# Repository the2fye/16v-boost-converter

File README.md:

# 16 V Boost Converter for a 2S2P Li-ion Pack

A compact DC-DC boost converter that takes a 2S2P lithium-ion battery pack (7.2 V to 8.4 V) up to a regulated 16 V rail. I designed it as the technical assessment for the hardware team at the UGA Small Satellite Research Laboratory (SSRL), so the design choices lean toward what matters on a CubeSat: small board area, margin on every part, and protecting the battery.

## Specs

| Parameter | Value |
|---|---|
| Input | 7.2 V to 8.4 V (2S2P Li-ion), turn-on near 6.6 V |
| Output | 16 V (15.98 V set point) |
| Output current | 1 A assumed (16 W) |
| Controller | TI TPS55340PWP, HTSSOP-14 with PowerPAD |
| Switching frequency | 500 kHz |
| Duty cycle | 0.49 to 0.56 |
| Peak inductor current | 2.8 A |
| Estimated efficiency | 90% to 92% |
| Calculated output ripple | about 25 mV |
| PCB | 2 layers, 22.7 mm x 20.8 mm |
| Parts cost | about $8.16 per board (qty 1) |

## Design decisions

**Topology.** The input is always below 16 V, so a plain boost is the simplest option that works. I went non-synchronous (Schottky diode instead of a second MOSFET) because at 16 W a synchronous design would add a controller, two FETs, and more board area for a few percent of efficiency.

**Controller.** The TPS55340 has an integrated 5 A / 40 V switch, a 2.9 V to 32 V input range, adjustable frequency, and good TI design support (datasheet equations plus WEBENCH to cross-check). I compared it against the LM2577-ADJ (fixed 52 kHz, needs a much bigger inductor) and a synchronous controller like the LM5122 (more parts and layout complexity).

**Load current.** The assignment didn't give a load current, so I assumed 1 A and designed everything around it. At minimum input the switch and inductor carry about 2.5x the output current, which puts the peak near 2.8 A against the IC's 5.25 A current-limit floor.

**Inductor.** 12 uH Wurth 744393465120, sized for about 30% ripple. I picked it over a Coilcraft XAL8080 and a Bourns SRP1050WA because it had the smallest footprint, a 9.8 A saturation current, and AEC-Q200 qualification.

**Output caps.** Three 22 uF / 25 V X7R 1210 ceramics. Ceramics lose a lot of capacitance under DC bias (each one is closer to 15 uF at 16 V), so three in parallel gives about 45 uF effective and splits the ripple current.

**Feedback.** R1 = 120k, R2 = 10k gives Vout = 1.229 x (1 + 120k/10k) = 15.98 V.

**Battery undervoltage lockout.** The TPS55340's built-in UVLO sits below 3 V, which is way too low for a 2S pack. A boost pulls more current as its input drops, so a dying pack gets pulled down harder. I added a divider on EN (R5 = 51.1k, R6 = 10k) so the converter only runs above about 6.6 V.

**Compensation.** R3, C8, and C10 are starting values from the TI datasheet example. The right-half-plane zero at minimum input puts the crossover limit around 14 kHz, and the final values would come from a measured loop response.

## WEBENCH cross-check

To check my hand calculations, I ran the same specs (7.2 V to 8.4 V in, 16 V at 1 A out) through TI WEBENCH and compared against two TPS55340 designs it generated. WEBENCH picks its own frequency and parts (and used the QFN package), so this is a check on the math, not a copy of my board.

| | My design | WEBENCH design A | WEBENCH design B |
|---|---|---|---|
| Feedback divider | 120k / 10k | 120k / 10k | 120k / 10k |
| Duty cycle | 0.49 to 0.56 | about 0.49 to 0.56 | about 0.49 to 0.56 |
| Switching frequency | 500 kHz | 549 kHz | 779 kHz |
| Frequency resistor | 95.3k | 86.6k | 60.4k |
| Inductor | 12 uH | 10 uH | 6.8 uH |
| Output caps | 3x 22 uF | 2x 22 uF + 1 uF | 3x 4.7 uF |
| Compensation (R / C / C) | 2.55k / 0.1 uF / 100 pF | 976 / 150 nF / 2.7 nF | n/a |
| Efficiency | 90% to 92% (my estimate) | 95% to 96% | 95% to 96% |

What I took from it:

- **The feedback divider and duty cycle match exactly**, so the output setpoint and operating point math checks out.
- **The frequency equation holds.** Plugging 549 kHz into the datasheet equation gives 86.7k, which rounds to WEBENCH's 86.6k. That's the same equation I used to get 95.3k at 500 kHz.
- **The inductor difference comes from frequency, not a mistake.** The same sizing equation gives about 9.6 uH at 549 kHz (so 10 uH works) and about 10.5 uH at 500 kHz (so I rounded up to 12 uH).
- **Frequency barely moved efficiency.** Going from 549 kHz to 779 kHz cut the footprint about 39% with basically the same efficiency curve, which backs up that switching loss is secondary at this power level.
- **I think WEBENCH's efficiency is optimistic.** The Schottky diode alone drops about 0.5 V at 1 A, which is 0.5 W or about 3% of the 16 W output before counting the switch, inductor, or switching losses. I kept my 90% to 92% estimate.
- **For compensation**, I kept the datasheet's worked example values, since those come with documented equations. Either set is a starting point to tune on the bench.

## Schematic

## PCB layout

- Two layers: all parts and almost all routing on top, solid ground pour on the bottom.
- The critical switching loop (SW pins, D1, output caps, back to PGND) is kept under about 1 cm².
- Six thermal vias under the PowerPAD carry heat into the ground plane. This matters more in orbit, where there's no air to carry heat away.
- AGND and PGND join at the PowerPAD. The quiet analog parts return to ground near the IC, away from the switching return.
- No traces or vias under the inductor.
- Test points on the switch node, ground, and FB for bench bring-up.

## Repo contents

```
hardware/      KiCad 9 project (schematic, PCB, project file)
docs/          full design report (PDF) and images
production/    gerbers and BOM
```

The KiCad files open directly. The TPS55340 and Wurth inductor footprints are embedded in the board file.

## Full report

The [design report](docs/Boost_Converter_Design_Report_Aryafar.pdf) covers the full calculations, the inductor trade study, the loss breakdown, and an 11-step bench test procedure. Note that the report lists the board as 22.3 mm wide. The actual outline in the PCB file is 22.7 mm.

## Status and next steps

The design was completed on paper and in KiCad. It hasn't been fabricated yet. Things I'd change for a next revision:

- Finalize the compensation values with a measured loop response
- Add a 0 Ω footprint in series with R1 for loop injection
- Add a load switch so the pack can be fully disconnected at low charge
- Add an input fuse or eFuse for output short protection
- Widen the VIN and switch-node traces, and raise the silkscreen text to the fab minimum
- For flight: TPS55340-Q1, conformal coating, and thermal testing in vacuum

## Tools

KiCad 9, TI WEBENCH, DigiKey and Mouser for part selection.

## Project history

I did this design over about a week in September 2026 for the SSRL assessment and worked on it locally in KiCad without version control. The files here are the final version I submitted, added to GitHub in November 2026 and split into commits by part of the design (schematic, layout, production files, documentation). The only change from the submitted version is a BOM correction listing C1/C2 as X5R, which matches the actual Murata part.

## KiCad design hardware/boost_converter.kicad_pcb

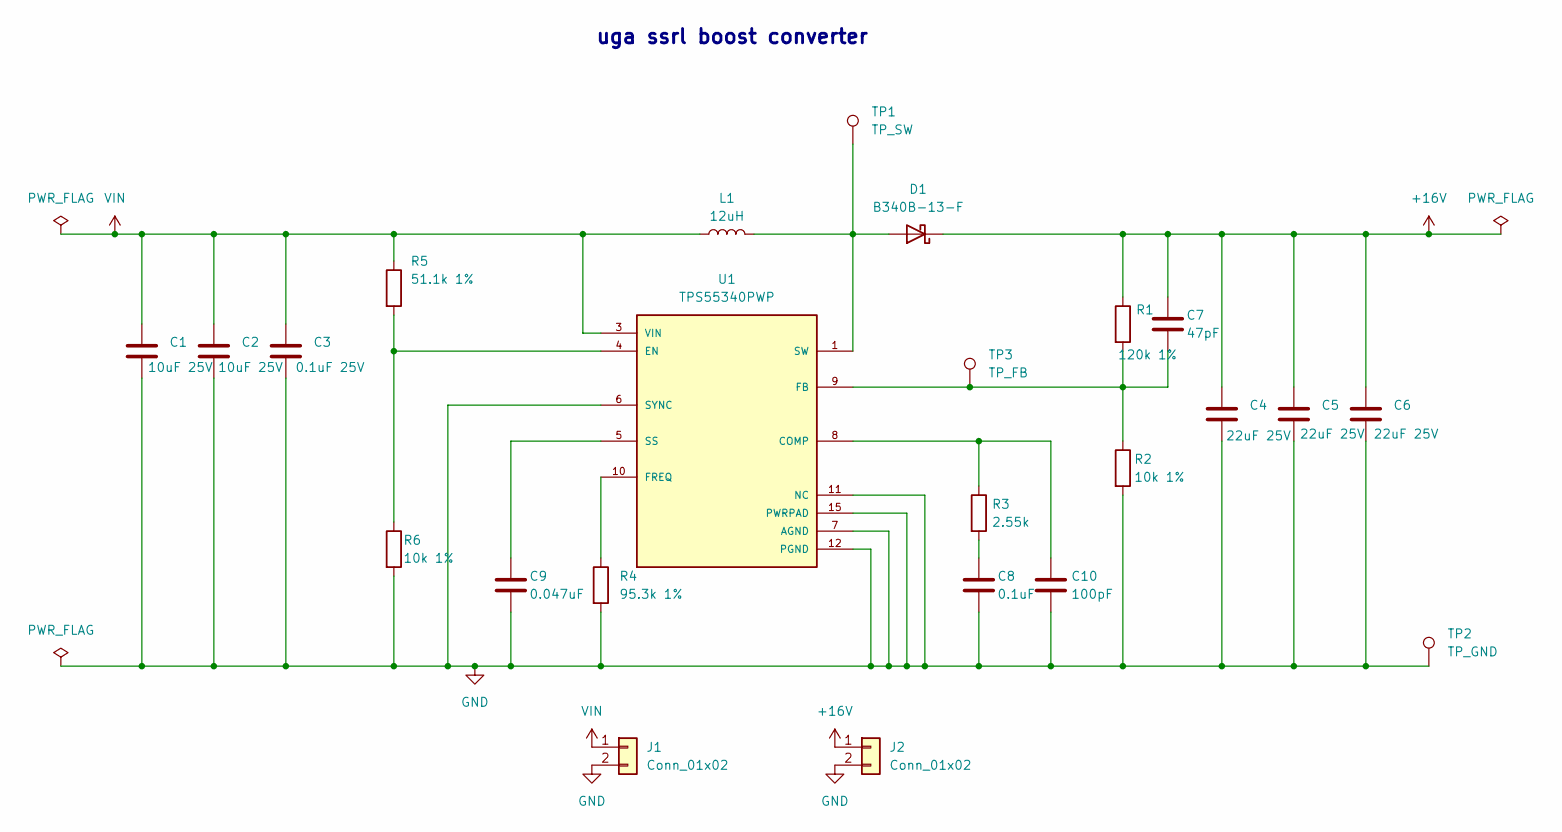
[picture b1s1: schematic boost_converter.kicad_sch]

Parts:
C1, C2: 10uF 25V; C_0805_2012Metric; MPN Murata GRM21BR61E106KA73L
C3: 0.1uF 25V; C_0603_1608Metric; MPN Murata GRM188R71E104KA01D
C4, C5, C6: 22uF 25V; C_1210_3225Metric; MPN Murata GRM32ER71E226KE15L
C7: 47pF; C_0603_1608Metric; MPN Murata GRM1885C1H470JA01D
C8: 0.1uF; C_0603_1608Metric; MPN Murata GRM188R71H104KA93D
C9: 0.047uF; C_0603_1608Metric; MPN Murata GRM188R71H473KA61D
C10: 100pF; C_0603_1608Metric; MPN Murata GRM1885C1H101JA01D
D1: B340B-13-F; D_SMB; MPN Diodes Inc. B340B-13-F
J1, J2: Conn_01x02; PinHeader_1x02_P2.54mm_Vertical; MPN Würth 61300211121
L1: 12uH; 744393465120; MPN Würth 744393465120
R1: 120k 1%; R_0603_1608Metric; MPN Yageo RC0603FR-07120KL
R2, R6: 10k 1%; R_0603_1608Metric; MPN Yageo RC0603FR-0710KL
R3: 2.55k; R_0603_1608Metric; MPN Yageo RC0603FR-072K55L
R4: 95.3k 1%; R_0603_1608Metric; MPN Yageo RC0603FR-0795K3L
R5: 51.1k 1%; R_0603_1608Metric; MPN Yageo RC0603FR-0751K1L
TP1: TP_SW; TestPoint_Pad_1.5x1.5mm
TP2: TP_GND; TestPoint_Pad_1.5x1.5mm
TP3: TP_FB; TestPoint_Pad_1.5x1.5mm
U1: TPS55340PWP; IC_TPS55340PWP; PARTREV E

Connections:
+16V: C4.1, C5.1, C6.1, C7.1, D1.1 (K), J2.1, R1.1
GND: C1.2, C2.2, C3.2, C4.2, C5.2, C6.2, C8.2, C9.2, C10.2, J1.2, J2.2, R2.2, R4.2, R6.2, TP2.1, U1.6 (SYNC), U1.7 (AGND), U1.11 (NC), U1.12 (PGND), U1.13 (PGND), U1.14 (PGND), U1.15 (PWRPAD), U1.16 (PWRPAD), U1.17 (PWRPAD), U1.18 (PWRPAD), U1.19 (PWRPAD), U1.20 (PWRPAD), U1.21 (PWRPAD)
unnamed: C8.1, R3.2
unnamed: D1.2 (A), L1.2, TP1.1, U1.1 (SW), U1.2 (SW)
unnamed: C10.1, R3.1, U1.8 (COMP)
unnamed: R5.2, R6.1, U1.4 (EN)
unnamed: C7.2, R1.2, R2.1, TP3.1, U1.9 (FB)
unnamed: R4.1, U1.10 (FREQ)
unnamed: C9.1, U1.5 (SS)
VIN: C1.1, C2.1, C3.1, J1.1, L1.1, R5.1, U1.3 (VIN)

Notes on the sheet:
uga ssrl boost converter

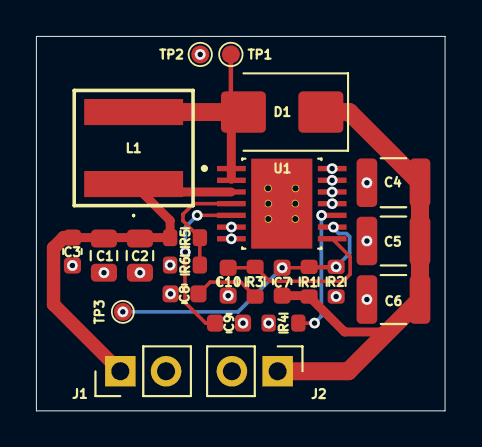
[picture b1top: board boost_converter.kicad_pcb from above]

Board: 2 copper layers, 22.7 x 20.8 mm, 24 parts (0 on the bottom side), 10 nets.

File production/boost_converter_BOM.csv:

Item,Qty,Reference(s),Value,Description,Manufacturer,Mfr Part Number,Footprint / Package,Unit Price (USD),Ext. Price (USD),Notes
1,2,"C1, C2",10uF 25V,"MLCC, 10 uF, 25 V, X5R",Murata,GRM21BR61E106KA73L,0805 (2012 metric),$0.12,$0.24,Input bulk
2,1,C3,0.1uF 25V,"MLCC, 0.1 uF, 25 V, X7R",Murata,GRM188R71E104KA01D,0603 (1608 metric),$0.03,$0.03,Input HF bypass
3,3,"C4, C5, C6",22uF 25V,"MLCC, 22 uF, 25 V, X7R",Murata,GRM32ER71E226KE15L,1210 (3225 metric),$0.40,$1.20,Output caps
4,1,C7,47pF,"MLCC, 47 pF, 50 V, C0G/NP0",Murata,GRM1885C1H470JA01D,0603 (1608 metric),$0.03,$0.03,FB feedforward
5,1,C8,0.1uF,"MLCC, 0.1 uF, 50 V, X7R",Murata,GRM188R71H104KA93D,0603 (1608 metric),$0.03,$0.03,COMP
6,1,C9,0.047uF,"MLCC, 0.047 uF, 50 V, X7R",Murata,GRM188R71H473KA61D,0603 (1608 metric),$0.03,$0.03,Soft-start
7,1,C10,100pF,"MLCC, 100 pF, 50 V, C0G/NP0",Murata,GRM1885C1H101JA01D,0603 (1608 metric),$0.03,$0.03,COMP
8,1,D1,B340B-13-F,"Schottky diode, 40 V, 3 A",Diodes Inc.,B340B-13-F,SMB (DO-214AA),$0.55,$0.55,Rectifier
9,2,"J1, J2",Conn 1x02,"Pin header, 2 pin, 2.54 mm",Wurth,61300211121,1x02 THT 2.54mm,$0.11,$0.22,Input / Output
10,1,L1,12uH,"Power inductor, 12 uH, shielded",Wurth,744393465120,L-Code SMD,$2.38,$2.38,Verified (Mouser)
11,1,R1,120k 1%,"Thick film resistor, 120 k, 1%",Yageo,RC0603FR-07120KL,0603 (1608 metric),$0.02,$0.02,FB top
12,2,"R2, R6",10k 1%,"Thick film resistor, 10 k, 1%",Yageo,RC0603FR-0710KL,0603 (1608 metric),$0.02,$0.04,FB bottom / EN
13,1,R3,2.55k 1%,"Thick film resistor, 2.55 k, 1%",Yageo,RC0603FR-072K55L,0603 (1608 metric),$0.02,$0.02,COMP
14,1,R4,95.3k 1%,"Thick film resistor, 95.3 k, 1%",Yageo,RC0603FR-0795K3L,0603 (1608 metric),$0.02,$0.02,FREQ (500 kHz)
15,1,R5,51.1k 1%,"Thick film resistor, 51.1 k, 1%",Yageo,RC0603FR-0751K1L,0603 (1608 metric),$0.02,$0.02,EN UVLO
16,1,TP1,TP_SW,"Test point, bare Cu pad",-,(PCB feature),1.0 mm pad,$0.00,$0.00,Switch node probe
17,1,TP2,TP_GND,"Test point, bare Cu pad",-,(PCB feature),1.0 mm pad,$0.00,$0.00,Ground reference
18,1,TP3,TP_FB,"Test point, bare Cu pad",-,(PCB feature),1.0 mm pad,$0.00,$0.00,Feedback probe
19,1,U1,TPS55340PWP,"Boost/SEPIC/flyback regulator, 5 A",Texas Instruments,TPS55340PWP,HTSSOP-14 (PowerPAD),$3.30,$3.30,Verified (DigiKey)
Totals,24,,,,,,,Total,$8.16,
